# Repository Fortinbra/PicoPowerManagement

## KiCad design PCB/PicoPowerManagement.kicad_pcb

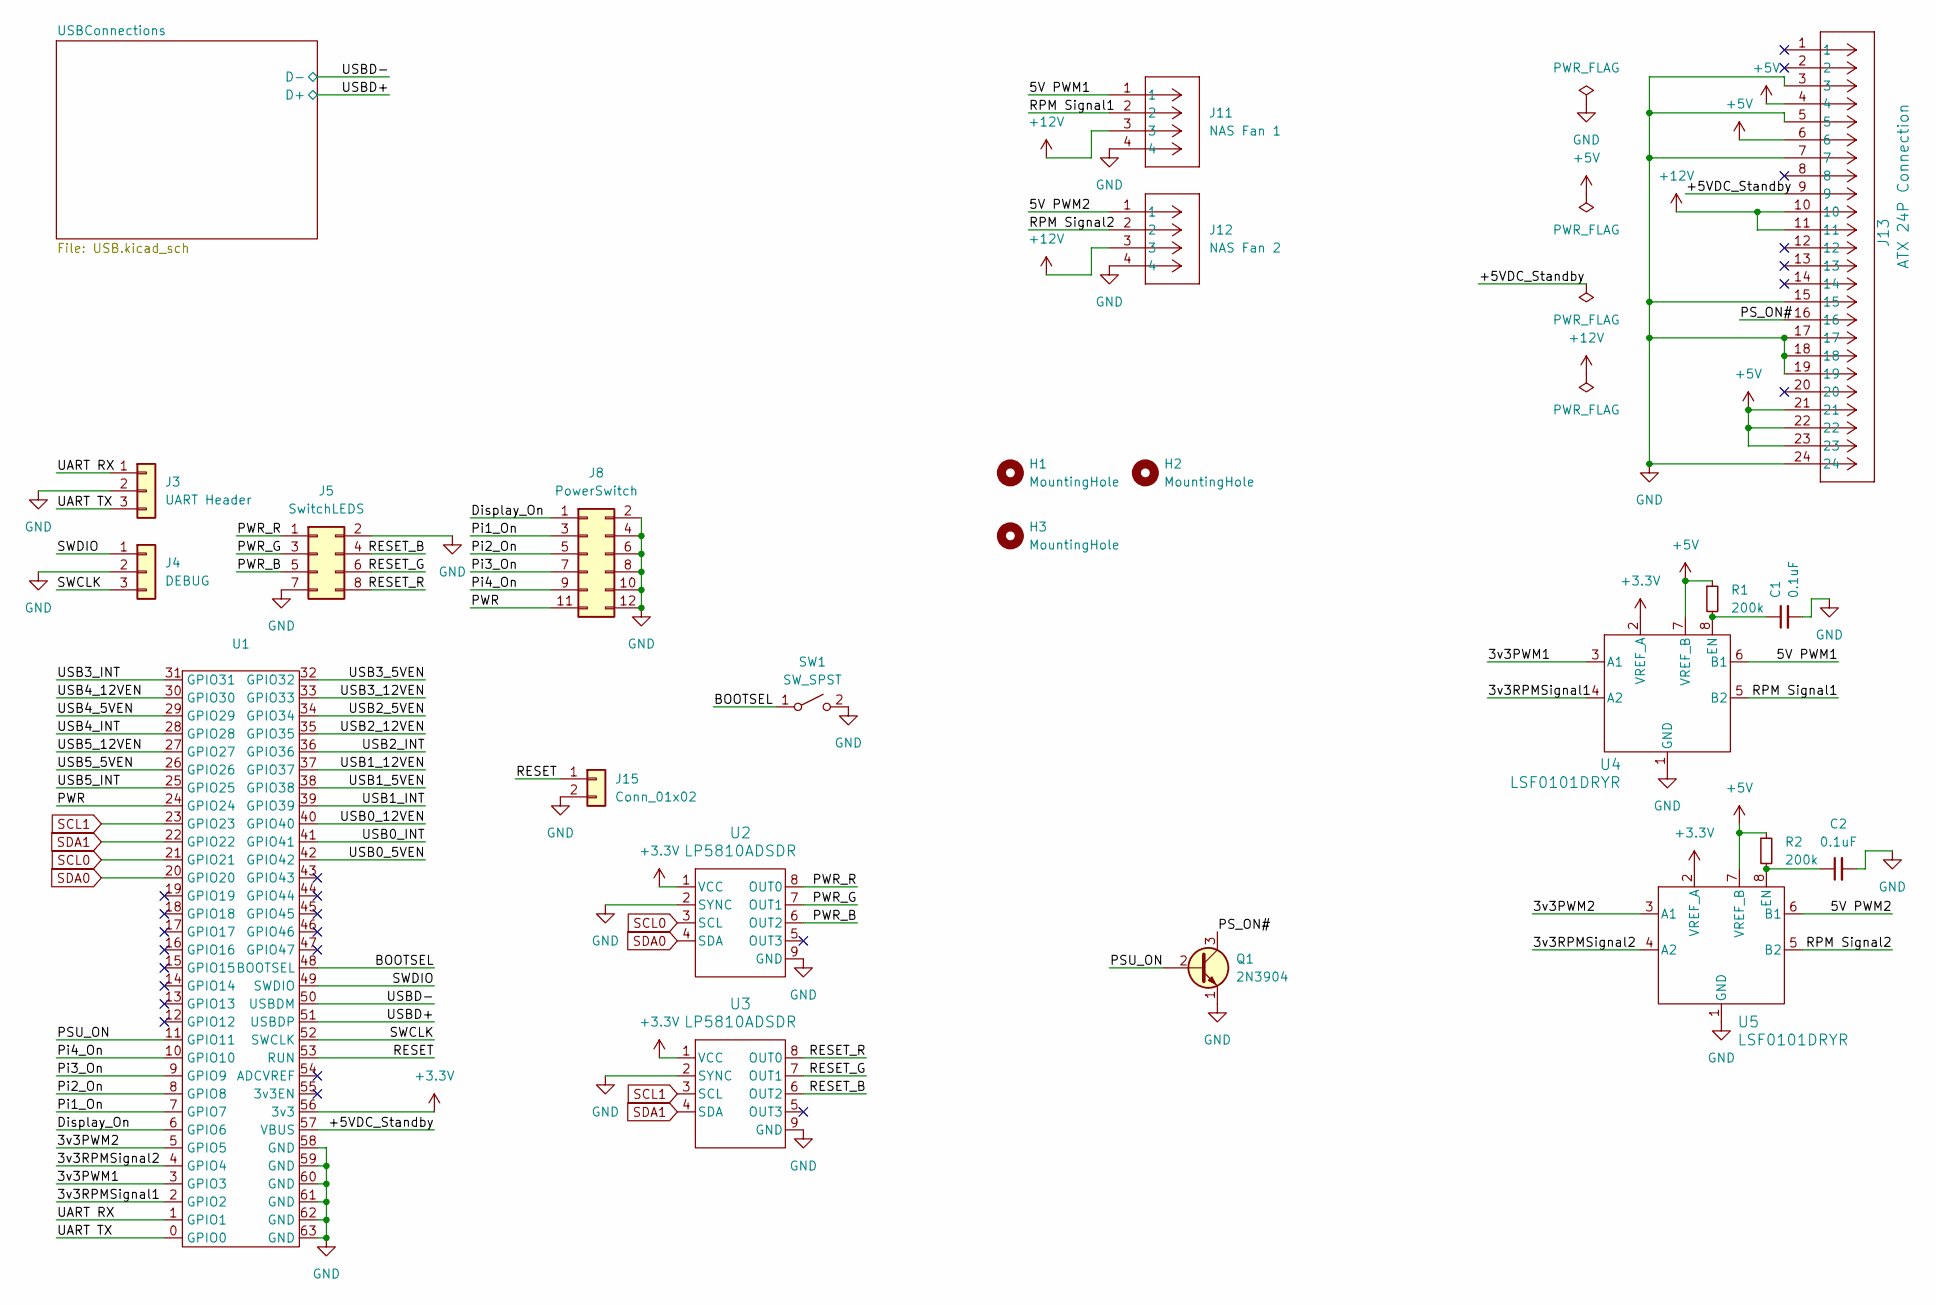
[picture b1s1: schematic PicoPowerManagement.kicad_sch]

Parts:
C1, C2: 0.1uF; C_0603_1608Metric_Pad1.08x0.95mm_HandSolder
H1, H2, H3: MountingHole; MountingHole_3mm
J3: UART Header; PinHeader_1x03_P2.54mm_Vertical
J4: DEBUG; PinHeader_1x03_P2.54mm_Vertical
J5: SwitchLEDS; PinHeader_2x04_P2.54mm_Vertical
J8: PowerSwitch; PinHeader_2x06_P2.54mm_Vertical
J11: NAS Fan 1; CONN_SD-47053-001_H10p00_MOL
J12: NAS Fan 2; CONN_SD-47053-001_H10p00_MOL
J13: ATX 24P Connection; CONN_5566-24_MOL
J15: Conn_01x02; PinHeader_1x02_P2.54mm_Vertical
Q1: 2N3904; TO92254P460H750-3
R1, R2: 200k; R_0603_1608Metric_Pad0.98x0.95mm_HandSolder
SW1: SW_SPST; Panasonic_EVQPUJ_EVQPUA
U1: PGA2350
U2, U3: LP5810ADSDR; DSD0008B-MFG
U4, U5: LSF0101DRYR; DCU0008A_L

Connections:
+3.3V: U1.56 (3v3), U2.1 (VCC), U3.1 (VCC), U4.2 (VREF_A), U5.2 (VREF_A)
+5V: J13.4, J13.6, J13.21, J13.22, J13.23, R1.1, R2.1, U4.7 (VREF_B), U5.7 (VREF_B); also elsewhere on the board
+12V: J11.3, J12.3, J13.10, J13.11; also elsewhere on the board
/3v3PWM1: U1.3 (GPIO3), U4.3 (A1)
/3v3PWM2: U1.5 (GPIO5), U5.3 (A1)
/3v3RPMSignal1: U1.2 (GPIO2), U4.4 (A2)
/3v3RPMSignal2: U1.4 (GPIO4), U5.4 (A2)
/5V PWM1: J11.1, U4.6 (B1)
/5V PWM2: J12.1, U5.6 (B1)
/+5VDC_Standby: J13.9, U1.57 (VBUS)
/BOOTSEL: SW1.1 (A), U1.48 (BOOTSEL)
/Display_On: J8.1, U1.6 (GPIO6)
/PSU_ON: Q1.2 (B), U1.11 (GPIO11)
/PS_ON#: J13.16, Q1.3 (C)
/PWR: J8.11, U1.24 (GPIO24)
/PWR_B: J5.5, U2.6 (OUT2)
/PWR_G: J5.3, U2.7 (OUT1)
/PWR_R: J5.1, U2.8 (OUT0)
/Pi1_On: J8.3, U1.7 (GPIO7)
/Pi2_On: J8.5, U1.8 (GPIO8)
/Pi3_On: J8.7, U1.9 (GPIO9)
/Pi4_On: J8.9, U1.10 (GPIO10)
/RESET: J15.1, U1.53 (RUN)
/RESET_B: J5.4, U3.6 (OUT2)
/RESET_G: J5.6, U3.7 (OUT1)
/RESET_R: J5.8, U3.8 (OUT0)
/RPM Signal1: J11.2, U4.5 (B2)
/RPM Signal2: J12.2, U5.5 (B2)
/SWCLK: J4.3, U1.52 (SWCLK)
/SWDIO: J4.1, U1.49 (SWDIO)
/UART RX: J3.1, U1.1 (GPIO1)
/UART TX: J3.3, U1.0 (GPIO0)
/USB0_5VEN: U1.42 (GPIO42)
/USB0_12VEN: U1.40 (GPIO40)
/USB0_INT: U1.41 (GPIO41)
/USB1_5VEN: U1.38 (GPIO38)
/USB1_12VEN: U1.37 (GPIO37)
/USB1_INT: U1.39 (GPIO39)
/USB2_5VEN: U1.34 (GPIO34)
/USB2_12VEN: U1.35 (GPIO35)
/USB2_INT: U1.36 (GPIO36)
/USB3_5VEN: U1.32 (GPIO32)
/USB3_12VEN: U1.33 (GPIO33)
/USB3_INT: U1.31 (GPIO31)
/USB4_5VEN: U1.29 (GPIO29)
/USB4_12VEN: U1.30 (GPIO30)
/USB4_INT: U1.28 (GPIO28)
/USB5_5VEN: U1.26 (GPIO26)
/USB5_12VEN: U1.27 (GPIO27)
/USB5_INT: U1.25 (GPIO25)
/USBD+: U1.51 (USBDP); also elsewhere on the board
/USBD-: U1.50 (USBDM); also elsewhere on the board
GND: C1.2, C2.2, J3.2, J4.2, J5.2, J5.7, J8.2, J8.4, J8.6, J8.8, J8.10, J8.12, J11.4, J12.4, J13.3, J13.5, J13.7, J13.15, J13.17, J13.18, J13.19, J13.24, J15.2, Q1.1 (E), SW1.2 (B), U1.58 (GND), U1.59 (GND), U1.60 (GND), U1.61 (GND), U1.62 (GND), U1.63 (GND), U2.2 (SYNC), U2.9 (GND), U3.2 (SYNC), U3.9 (GND), U4.1 (GND), U5.1 (GND); also elsewhere on the board
unnamed: C1.1, R1.2, U4.8 (EN)
unnamed: C2.1, R2.2, U5.8 (EN)
SCL0: U1.21 (GPIO21), U2.3 (SCL)
SCL1: U1.23 (GPIO23), U3.3 (SCL)
SDA0: U1.20 (GPIO20), U2.4 (SDA)
SDA1: U1.22 (GPIO22), U3.4 (SDA)

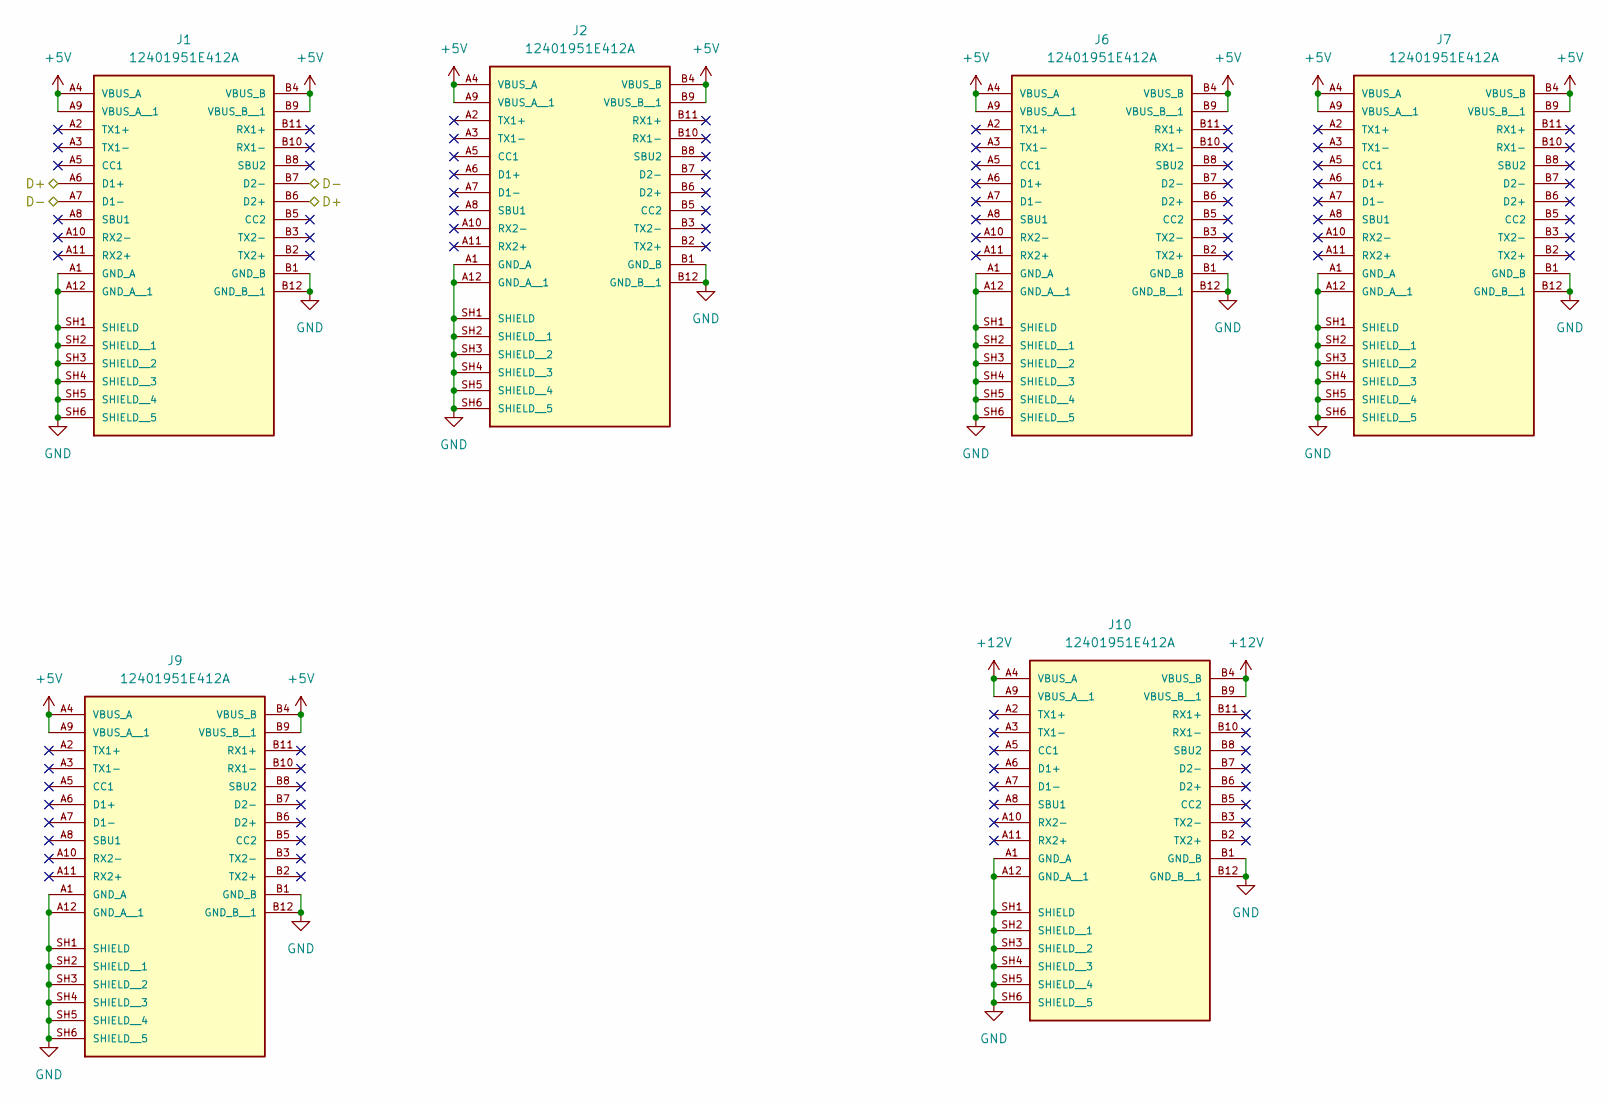
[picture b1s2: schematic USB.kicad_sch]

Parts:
J1, J2, J6, J7, J9, J10: 12401951E412A; AMPHENOL_12401951E412A; PARTREV 9

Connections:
+5V: J1.A4 (VBUS_A), J1.A9 (VBUS_A__1), J1.B4 (VBUS_B), J1.B9 (VBUS_B__1), J2.A4 (VBUS_A), J2.A9 (VBUS_A__1), J2.B4 (VBUS_B), J2.B9 (VBUS_B__1), J6.A4 (VBUS_A), J6.A9 (VBUS_A__1), J6.B4 (VBUS_B), J6.B9 (VBUS_B__1), J7.A4 (VBUS_A), J7.A9 (VBUS_A__1), J7.B4 (VBUS_B), J7.B9 (VBUS_B__1), J9.A4 (VBUS_A), J9.A9 (VBUS_A__1), J9.B4 (VBUS_B), J9.B9 (VBUS_B__1); also elsewhere on the board
+12V: J10.A4 (VBUS_A), J10.A9 (VBUS_A__1), J10.B4 (VBUS_B), J10.B9 (VBUS_B__1); also elsewhere on the board
/USBD+: J1.A6 (D1+), J1.B6 (D2+); also elsewhere on the board
/USBD-: J1.A7 (D1-), J1.B7 (D2-); also elsewhere on the board
GND: J1.A1 (GND_A), J1.A12 (GND_A__1), J1.B1 (GND_B), J1.B12 (GND_B__1), J1.SH1 (SHIELD), J1.SH2 (SHIELD__1), J1.SH3 (SHIELD__2), J1.SH4 (SHIELD__3), J1.SH5 (SHIELD__4), J1.SH6 (SHIELD__5), J2.A1 (GND_A), J2.A12 (GND_A__1), J2.B1 (GND_B), J2.B12 (GND_B__1), J2.SH1 (SHIELD), J2.SH2 (SHIELD__1), J2.SH3 (SHIELD__2), J2.SH4 (SHIELD__3), J2.SH5 (SHIELD__4), J2.SH6 (SHIELD__5), J6.A1 (GND_A), J6.A12 (GND_A__1), J6.B1 (GND_B), J6.B12 (GND_B__1), J6.SH1 (SHIELD), J6.SH2 (SHIELD__1), J6.SH3 (SHIELD__2), J6.SH4 (SHIELD__3), J6.SH5 (SHIELD__4), J6.SH6 (SHIELD__5), J7.A1 (GND_A), J7.A12 (GND_A__1), J7.B1 (GND_B), J7.B12 (GND_B__1), J7.SH1 (SHIELD), J7.SH2 (SHIELD__1), J7.SH3 (SHIELD__2), J7.SH4 (SHIELD__3), J7.SH5 (SHIELD__4), J7.SH6 (SHIELD__5), J9.A1 (GND_A), J9.A12 (GND_A__1), J9.B1 (GND_B), J9.B12 (GND_B__1), J9.SH1 (SHIELD), J9.SH2 (SHIELD__1), J9.SH3 (SHIELD__2), J9.SH4 (SHIELD__3), J9.SH5 (SHIELD__4), J9.SH6 (SHIELD__5), J10.A1 (GND_A), J10.A12 (GND_A__1), J10.B1 (GND_B), J10.B12 (GND_B__1), J10.SH1 (SHIELD), J10.SH2 (SHIELD__1), J10.SH3 (SHIELD__2), J10.SH4 (SHIELD__3), J10.SH5 (SHIELD__4), J10.SH6 (SHIELD__5); also elsewhere on the board

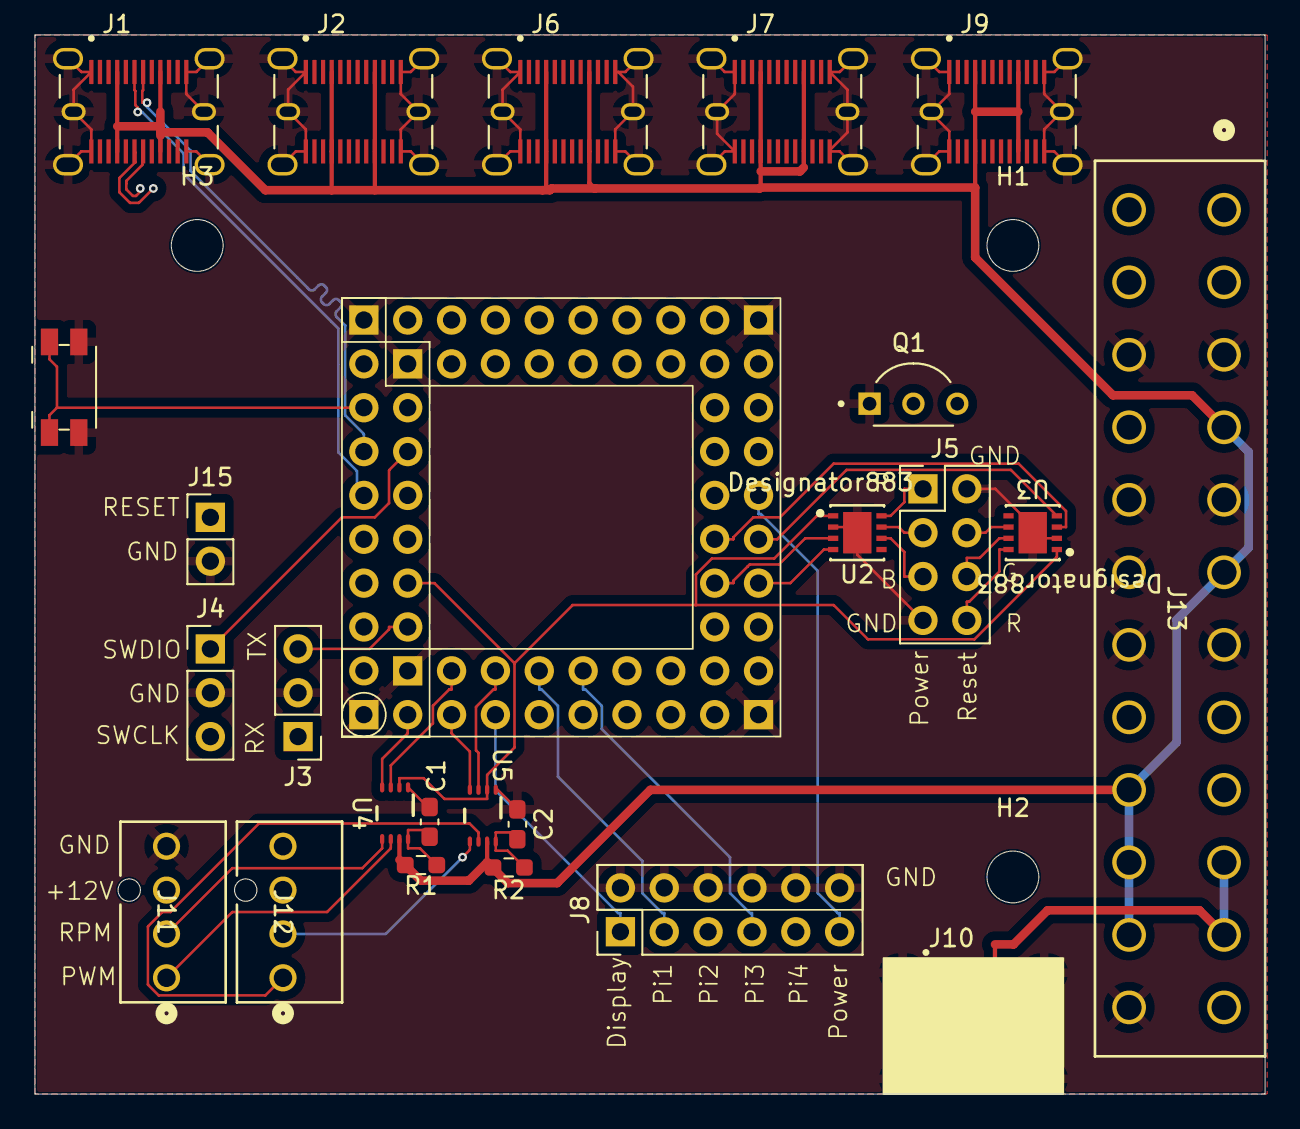
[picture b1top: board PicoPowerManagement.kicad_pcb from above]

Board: 4 copper layers, 71.2 x 61.3 mm, 28 parts (0 on the bottom side), 41 nets.

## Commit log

2025-02-18 Add comprehensive .gitignore for C++, CMake, Visual Studio, and Windows
2025-02-18 Add submodule for KiCad-RP-Pico library
2025-02-18 Add initial KiCad PCB files for PicoPowerManagement project
2025-02-19 Add footprint and symbol libraries for LSF0101DRYR and LSF0102DCUR components
2025-02-19 Update submodule for KiCad-RP-Pico library to latest commit
2025-02-24 Add initial implementation of PicoPowerManagement project with API and client setup
2025-02-24 Add initial project files and configuration for PicoPowerManagement
2025-02-25 Add UART and pin setup functionality for PicoPowerManagement project
2025-03-01 Add new pages and components for PicoPowerManagement client, update libraries, and modify project settings
2025-03-01 cleanup
2025-03-01 No code changes made.
2025-03-01 revamping
2025-03-06 confused now
2025-03-11 Add 2N3904 component library and update footprint and symbol definitions
2025-03-11 Update subproject commit reference for KiCad-RP-Pico library
2025-03-24 Upgrade to .NET 10.0 and update package references
    Updated target framework in `PicoPowerManagement.Api.csproj` and `PicoPowerManagement.Client.csproj` from `net9.0` to `net10.0`.
    Package references for .NET 10.0 preview versions have been applied, including `Microsoft.AspNetCore.Components.WebAssembly`, `Microsoft.AspNetCore.Components.WebAssembly.DevServer`, and `System.Text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
    Additionally, `Microsoft.FluentUI.AspNetCore.Components` packages have been upgraded to version `4.11.7` in the client project.
2025-03-28 updating rules and fixing footprints
2025-03-29 Enhance PCB design and update UI for Raspberry Pi models
    The most important changes in the `PicoPowerManagement.kicad_pcb` file focus on improving the PCB design's functionality and visual representation. Key updates include the removal of the option to pl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
    In the `PicoPowerManagement.kicad_pro` file, a new error check for "text_on_edge_cuts" was added to enhance the validation process. The `PicoPowerManagement.kicad_sch` files saw the addition of multip
2025-03-30 simplifying USB
2025-03-31 less confused
